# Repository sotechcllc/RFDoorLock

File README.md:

# RFDoorLock
Repo. for the RFID DoorLock project

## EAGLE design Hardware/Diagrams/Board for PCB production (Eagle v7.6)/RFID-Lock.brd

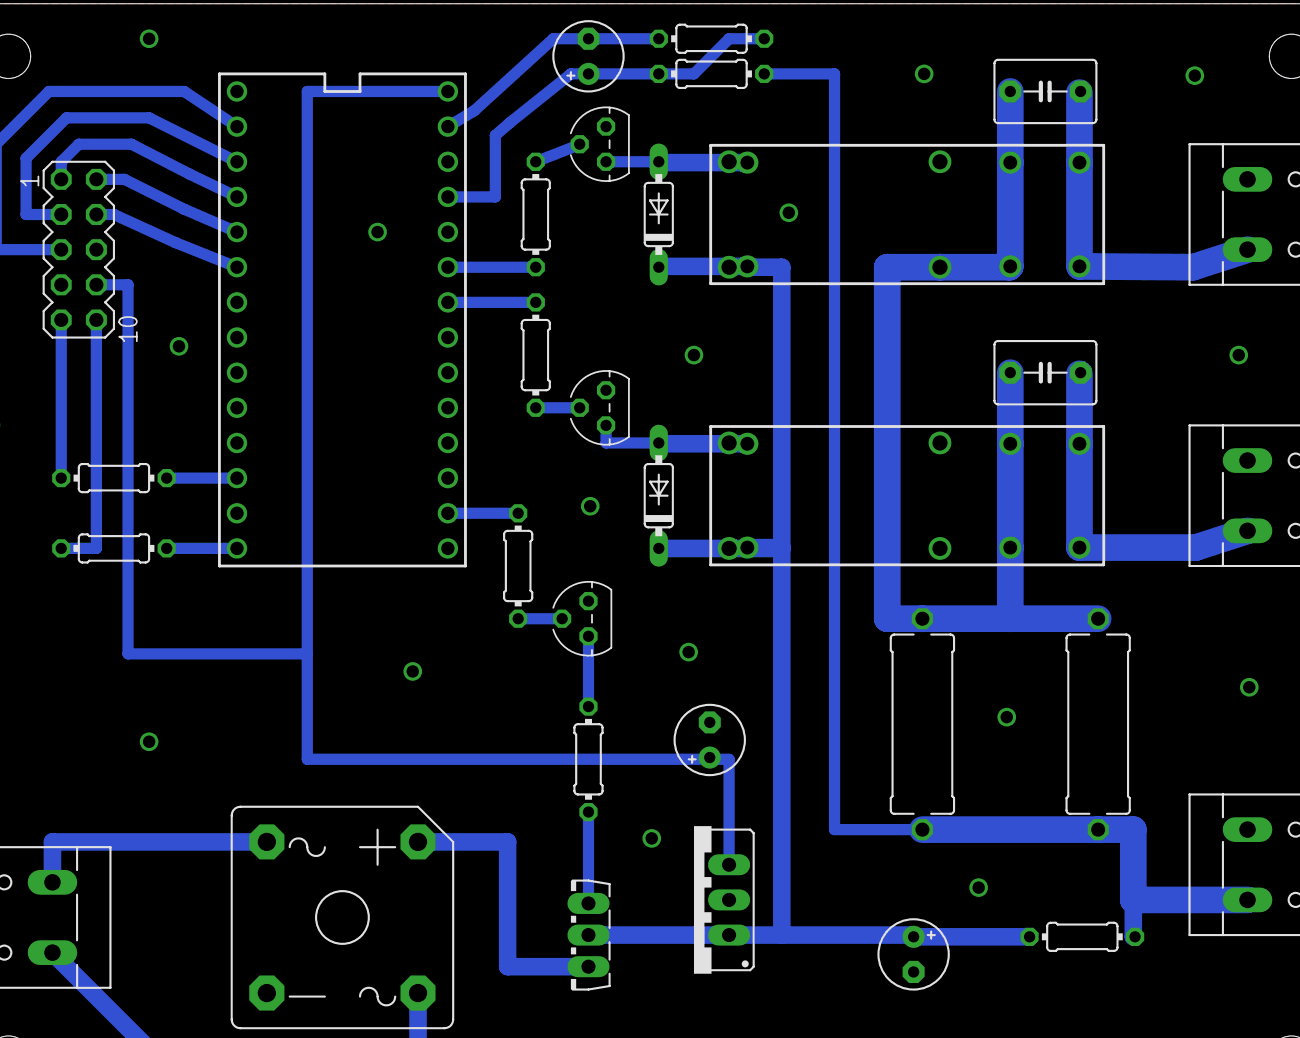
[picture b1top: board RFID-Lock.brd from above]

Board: 2 copper layers, 32 parts (0 on the bottom side), 31 nets.

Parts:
B1: GBPC6
C3, C5: 1 µF; E2,5-5
C4: 10 µF; E2,5-5
C6, C7: 330nF; C5B4.5
D1, D2: 1N4148; DO35-7
IC1: 7805; 78XXS
K1, K2: FINDER-43.61
Q1, Q2, Q4: BC547; TO92
Q3: BD680; TO126AV
R1, R2: 820; 0204/7
R3, R4, R7, R8: 10k; 0204/7
R5: 0.22; 0204/7
R6, R11: RX; P0613/15
R9: 220k 1%; 0204/7
R10: 15k 1%; 0204/7
SV2: PN532; MA05-2
X1: DOOR 2; W237-132
X2: DOOR 1; W237-132
X3: Battery; W237-132
X4: Transformator 12V~; W237-132
µPC: Teensy 3.1 / 3.2; TEENSY3-DIL

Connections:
+5V: C3.+, IC1.OUT, SV2.8, µPC.VIN
+12V: R5.2, R6.1, R9.2, R11.1, X3.2
AGND: C5.-, R10.1, µPC.AGND
DOOR2: C6.1, K1.14@1, K1.14@2, X1.2
GND: B1.-, C3.-, C4.-, IC1.GND, Q1.1, Q2.1, Q4.1, SV2.6, SV2.7, X1.1, X2.1, X3.1, µPC.GND
LED-GREEN: R1.1, SV2.9
LED-RED: R2.1, SV2.10
MISO: SV2.3, µPC.1
MOSI: SV2.4, µPC.4
unnamed: Q3.B, R7.1
unnamed: Q4.3, R7.2
unnamed: R1.2, µPC.10
unnamed: R2.2, µPC.12
unnamed: B1.AC1, X4.2
unnamed: D2.A, K2.A2, Q2.3
unnamed: Q4.2, R8.1
unnamed: C7.1, K2.14@1, K2.14@2, X2.2
unnamed: D1.A, K1.A2, Q1.3
unnamed: Q1.2, R4.2
unnamed: Q2.2, R3.2
unnamed: R4.1, µPC.21/A7
unnamed: R3.1, µPC.20/A6
unnamed: B1.+, Q3.E
unnamed: B1.AC2, X4.1
unnamed: C6.2, C7.2, K1.11@1, K1.11@2, K2.11@1, K2.11@2, R6.2, R11.2
unnamed: R8.2, µPC.14/A0
unnamed: C5.+, R9.1, R10.2, µPC.23/A9
RST_PDN: SV2.1, µPC.2
SCK: SV2.2, µPC.3
SSEL: SV2.5, µPC.0
V+: C4.+, D1.C, D2.C, IC1.IN, K1.A1, K2.A1, Q3.C, R5.1

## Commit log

2017-03-13 Uploaded all the documentation related to the door lock project on a teensy 3.2 module.
2017-03-13 Updated the libraries and added content for the WICED feather board.
